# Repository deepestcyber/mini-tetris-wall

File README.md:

# Mini Tetris Board

Mainly the PCB design (WIP)

Example:

# Planing and ideas
Wir sollten den von KiCAD gedachten Weg nehmen, und mit den Schematics anfangen. Damit haben wir dann auch zumindest eine
Plausibilitätsprüfung für's Netz.

Idee für die Platine: vergrößern auf die Außenmaße des unteren Rahmens (der Kasten für die Elektronik), Bohrlöcher mit vorsehen.
Dann können wir es direkt mit dem Rest verschrauben. Aufpassen, dass im Rand kein Metall in den Layern ist, um elektrisch von außen
getrennt zu bleiben! Daten für Größe könnte man vermutlich aus den Laserdaten nehmen. Nachteil: Platine ist nur befestigt, wenn
der Rahmen zu ist.

# TODOs:
* ~~Footprint für SMD-Shild Arduino Mega~~
* ~~Footprint für SMD-Shild Raspi~~
* Stiftleisten fuer alle Switches
* Stiftleisten fuer Status-LED strips
* Power Button
* USB-Port vom RasPi nach aussen
* USB-C power input?
    * USB-C power inlet with negotiation
    * https://www.komputer.de/zen/index.php?main_page=product_info&products_id=635&zenid=bo7534ob5tfdgg7ghbn8ceoa73
* Lueftung fuer StepDown converter einplanen?
    * Power budget fuer LED strips ist 5V * 24 * 16 * 60mA (~= 115W)
* ~~Dicke! Powerlines~~
* ~~SPI und ready line~~
* logic level shifter 5V->3V3 für Leitungen Arduino->Raspi
* DeepCyber Logo auf Platine!
* Name, revision, url des repos auf platine

# Löten?
Ich höre, JLCPCB macht einseitige Bestückung für Bauteile, die sie haben. Da wir nur Stift- und Buchsenleisten haben, könnte das was werden.

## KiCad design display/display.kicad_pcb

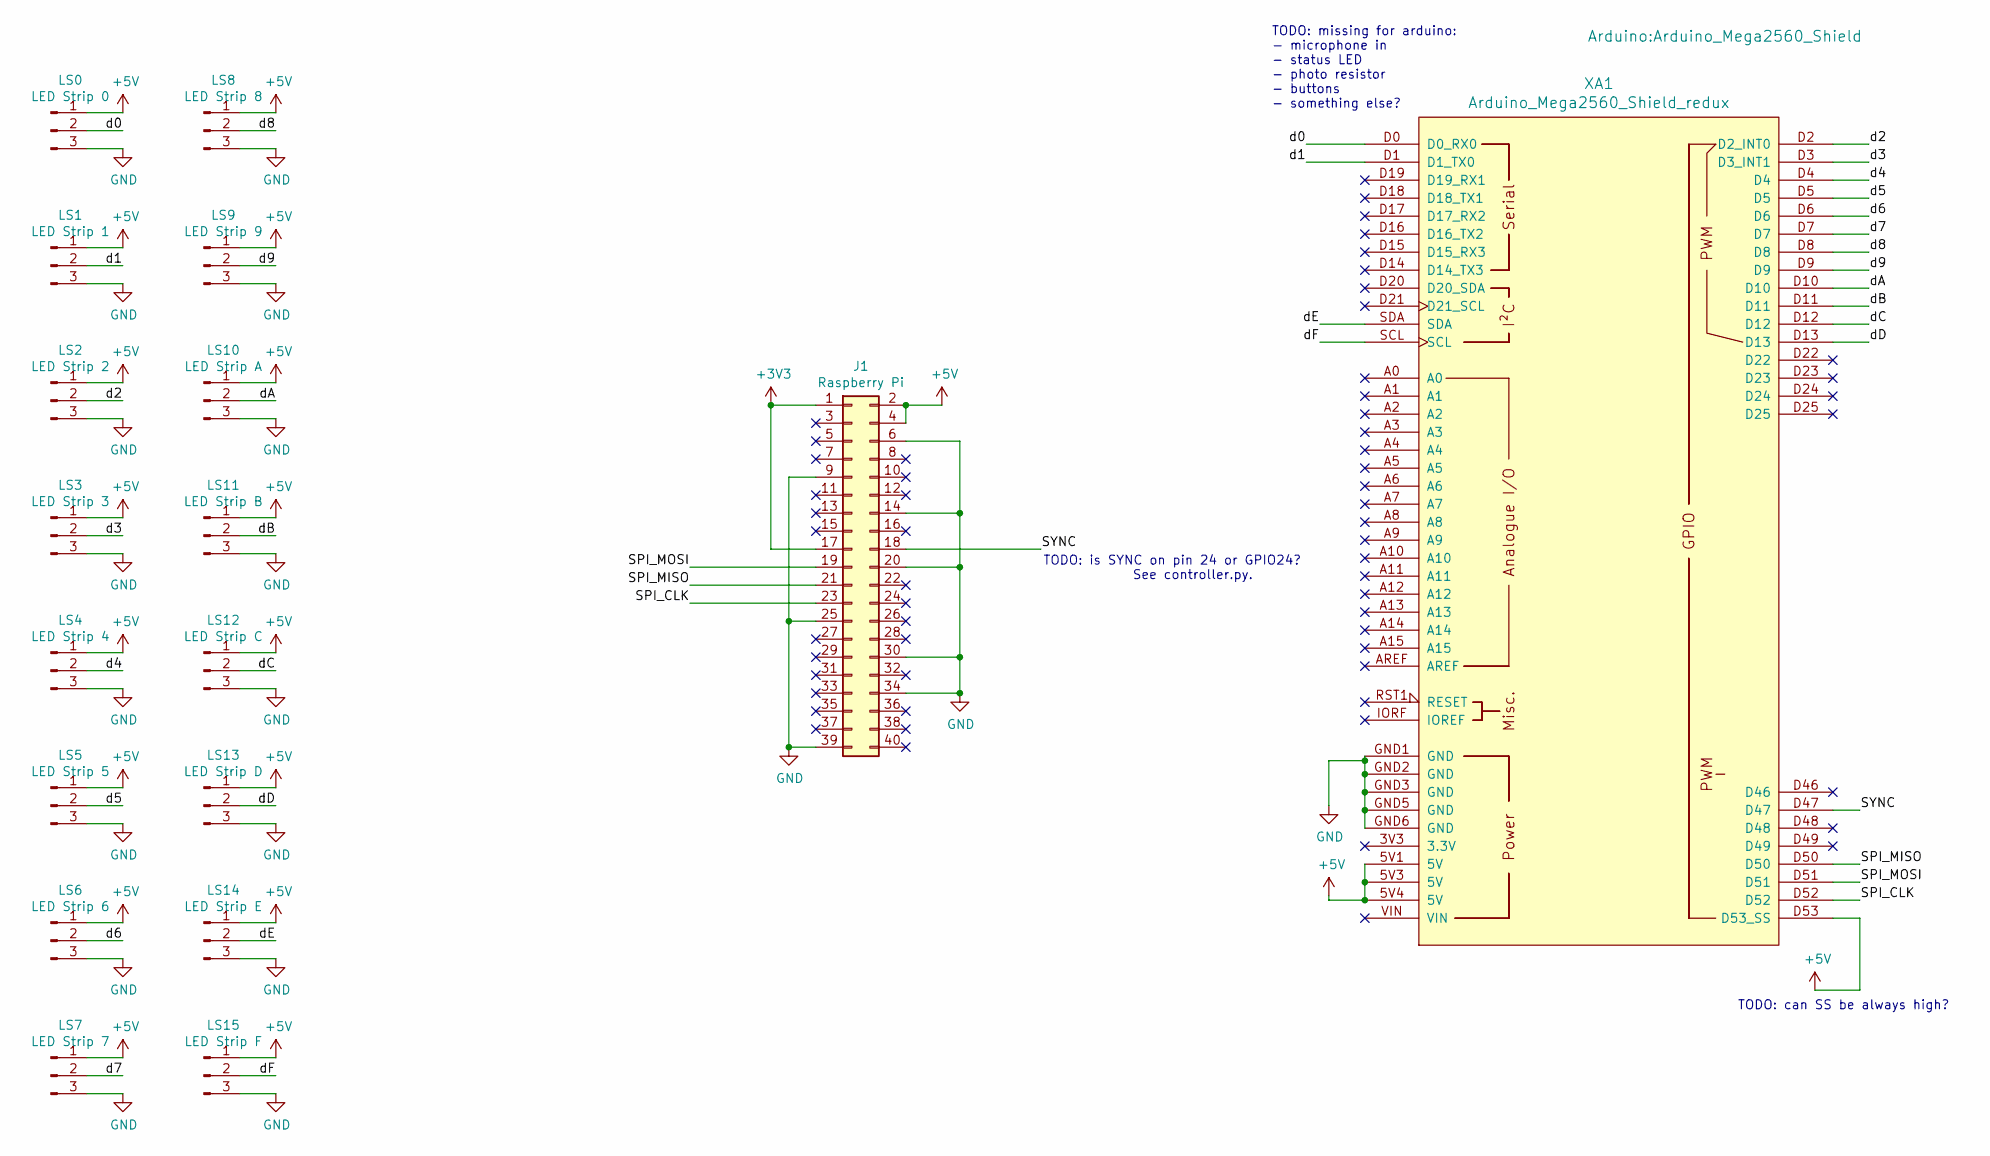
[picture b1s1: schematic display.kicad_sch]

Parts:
J1: Raspberry Pi; raspberrypi_2_3
LS0: LED Strip 0; strip_connector_hole
LS1: LED Strip 1; strip_connector_hole
LS2: LED Strip 2; strip_connector_hole
LS3: LED Strip 3; strip_connector_hole
LS4: LED Strip 4; strip_connector_hole
LS5: LED Strip 5; strip_connector_hole
LS6: LED Strip 6; strip_connector_hole
LS7: LED Strip 7; strip_connector_hole
LS8: LED Strip 8; strip_connector_hole
LS9: LED Strip 9; strip_connector_hole
LS10: LED Strip A; strip_connector_hole
LS11: LED Strip B; strip_connector_hole
LS12: LED Strip C; strip_connector_hole
LS13: LED Strip D; strip_connector_hole
LS14: LED Strip E; strip_connector_hole
LS15: LED Strip F; strip_connector_hole
XA1: Arduino_Mega2560_Shield_redux; Arduino_Mega2560_Shield

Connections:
+3V3: J1.1, J1.17
+5V: J1.2, J1.4, LS0.1, LS1.1, LS2.1, LS3.1, LS4.1, LS5.1, LS6.1, LS7.1, LS8.1, LS9.1, LS10.1, LS11.1, LS12.1, LS13.1, LS14.1, LS15.1, XA1.5V1 (5V), XA1.5V3 (5V), XA1.5V4 (5V), XA1.D53 (D53_SS); also elsewhere on the board
/SPI_CLK: J1.23, XA1.D52
/SPI_MISO: J1.21, XA1.D50
/SPI_MOSI: J1.19, XA1.D51
/SYNC: J1.18, XA1.D47
/d0: LS0.2, XA1.D0 (D0_RX0)
/d1: LS1.2, XA1.D1 (D1_TX0)
/d2: LS2.2, XA1.D2 (D2_INT0)
/d3: LS3.2, XA1.D3 (D3_INT1)
/d4: LS4.2, XA1.D4
/d5: LS5.2, XA1.D5
/d6: LS6.2, XA1.D6
/d7: LS7.2, XA1.D7
/d8: LS8.2, XA1.D8
/d9: LS9.2, XA1.D9
/dA: LS10.2, XA1.D10
/dB: LS11.2, XA1.D11
/dC: LS12.2, XA1.D12
/dD: LS13.2, XA1.D13
/dE: LS14.2, XA1.SDA
/dF: LS15.2, XA1.SCL
GND: J1.6, J1.9, J1.14, J1.20, J1.25, J1.30, J1.34, J1.39, LS0.3, LS1.3, LS2.3, LS3.3, LS4.3, LS5.3, LS6.3, LS7.3, LS8.3, LS9.3, LS10.3, LS11.3, LS12.3, LS13.3, LS14.3, LS15.3, XA1.GND1 (GND), XA1.GND2 (GND), XA1.GND3 (GND), XA1.GND5 (GND), XA1.GND6 (GND)

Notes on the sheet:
TODO: missing for arduino: - microphone in - status LED - photo resistor - buttons - something else?
TODO: can SS be always high?
TODO: is SYNC on pin 24 or GPIO24? See controller.py.

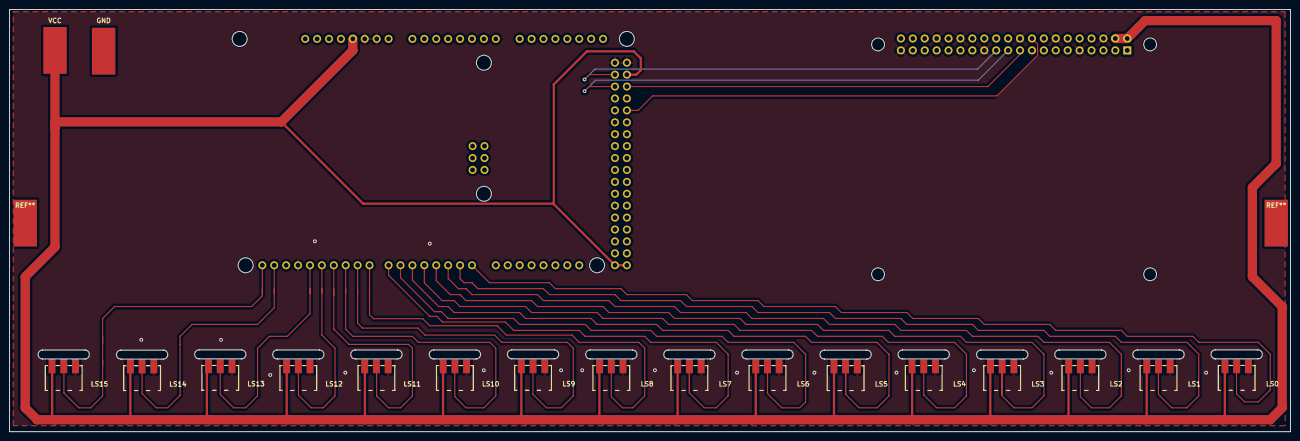
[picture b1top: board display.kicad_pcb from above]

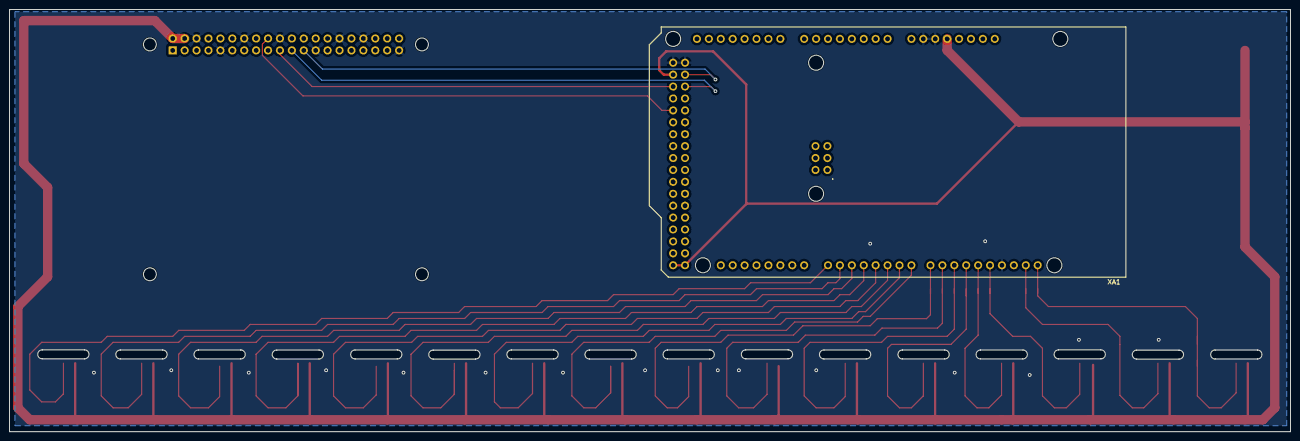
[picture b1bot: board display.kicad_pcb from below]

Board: 2 copper layers, 273.1 x 90.0 mm, 20 parts (2 on the bottom side), 23 nets.

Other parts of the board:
GND: GND; SolderWirePad_1x01_SMD_5x10mm
VCC: VCC; SolderWirePad_1x01_SMD_5x10mm

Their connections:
+5V: VCC.1; also elsewhere on the board

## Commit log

2021-03-02 Initial :3
2021-03-03 Connect all signals
2021-03-03 New board dimensions
    6mm spacing to left/right
    9cm absolute height
2021-03-03 For easier layouting prototype as svg
2021-03-04 PoC arduino pins
2021-03-11 WIP peer
2021-03-11 Add todos and stuff to readme
2021-03-17 TODO: Info auf platine silken
2024-07-30 Revive project
    - Hopefully correct footprint for Arduino Mega
    - Replaced all connectors with the one from the schematic footprint
    - Replaced pi header with the one from the schematic
    - Added infill (front & back) for easy grounding
    We can now proceed to wire everything up, mainly the connection between
    Arduino and Pi.
2024-07-30 Update to kicad 8
2024-07-30 Add SPI and SYNC pins
2024-09-19 Some progress with the peer
2024-09-24 Update to dos
2024-09-24 Forgot product link
